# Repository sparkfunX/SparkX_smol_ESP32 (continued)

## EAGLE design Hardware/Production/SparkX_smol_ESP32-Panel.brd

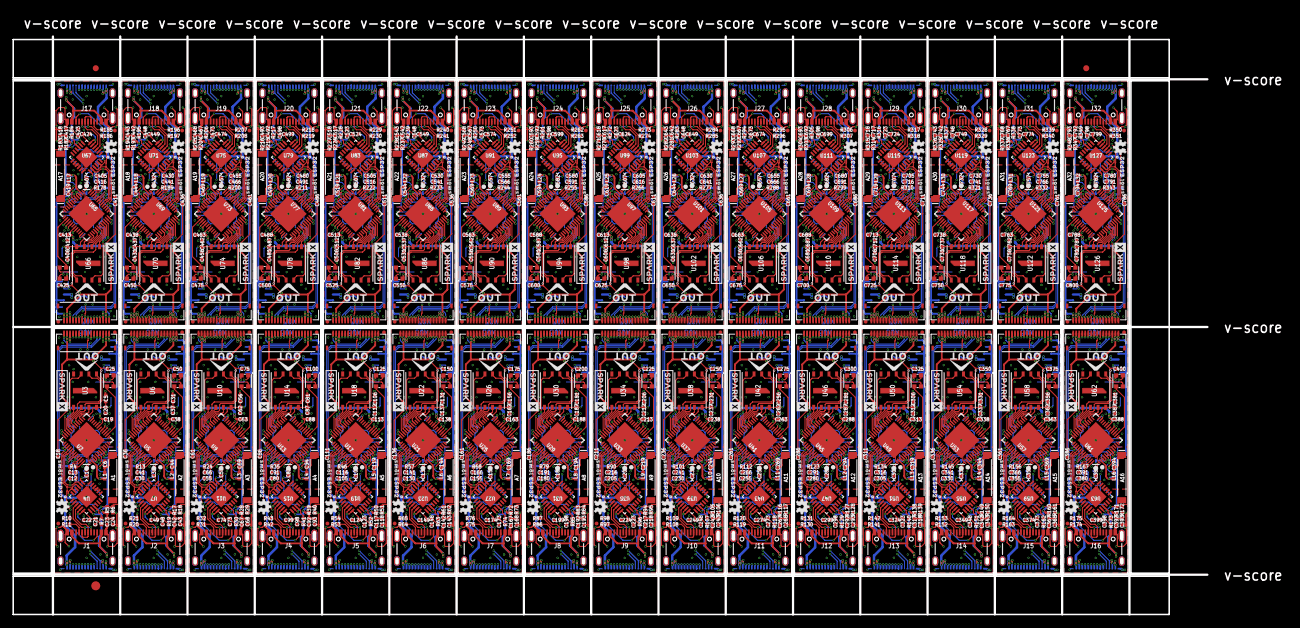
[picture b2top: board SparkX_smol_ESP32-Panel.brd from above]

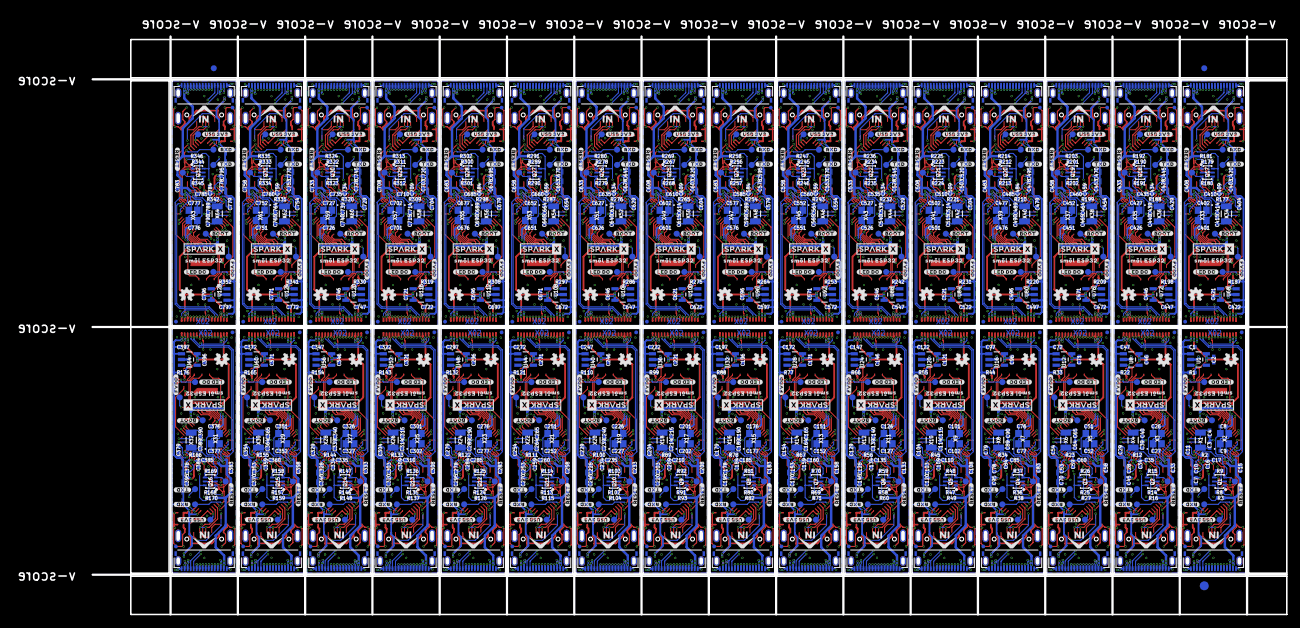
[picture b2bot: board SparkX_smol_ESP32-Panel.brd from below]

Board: 4 copper layers, 198.4 x 96.0 mm, 2470 parts (1379 on the bottom side), 1600 nets.

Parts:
!BOOT!, !BOOT!1, !BOOT!2, !BOOT!3, !BOOT!4, !BOOT!5, !BOOT!6, !BOOT!7, !BOOT!8, !BOOT!9, !BOOT!10, !BOOT!11, !BOOT!12, !BOOT!13, !BOOT!14, !BOOT!15, !BOOT!16, !BOOT!17, !BOOT!18, !BOOT!19, !BOOT!20, !BOOT!21, !BOOT!22, !BOOT!23, !BOOT!24, !BOOT!25, !BOOT!26, !BOOT!27, !BOOT!28, !BOOT!29, !BOOT!30, !BOOT!31: TEST-POINT3X4; PAD.03X.04
!RESET!, !RESET!1, !RESET!2, !RESET!3, !RESET!4, !RESET!5, !RESET!6, !RESET!7, !RESET!8, !RESET!9, !RESET!10, !RESET!11, !RESET!12, !RESET!13, !RESET!14, !RESET!15, !RESET!16, !RESET!17, !RESET!18, !RESET!19, !RESET!20, !RESET!21, !RESET!22, !RESET!23, !RESET!24, !RESET!25, !RESET!26, !RESET!27, !RESET!28, !RESET!29, !RESET!30, !RESET!31: TEST-POINT3X4; PAD.03X.04
A1, A2, A3, A4, A5, A6, A7, A8, A9, A10, A11, A12, A13, A14, A15, A16, A17, A18, A19, A20, A21, A22, A23, A24, A25, A26, A27, A28, A29, A30, A31, A32: ANTENNA2.4GHZ-8.0X1.0MM; ANT-2.4GHZ-8.0X1.0MM
C1, C2, C46, C47, C71, C72, C96, C97, C121, C122, C146, C147, C171, C172, C196, C197, C221, C222, C246, C247, C271, C272, C296, C297, C321, C322, C346, C347, C371, C372, C396, C397, C421, C422, C446, C447, C471, C472, C496, C497, C521, C522, C546, C547, C571, C572, C596, C597, C621, C622, C646, C647, C671, C672, C696, C697, C721, C722, C746, C747, C771, C772, C796, C797: 2.2uF; 0402-TIGHT
C3, C4, C39, C40, C64, C65, C89, C90, C114, C115, C139, C140, C164, C165, C189, C190, C214, C215, C239, C240, C264, C265, C289, C290, C314, C315, C339, C340, C364, C365, C389, C390, C414, C415, C439, C440, C464, C465, C489, C490, C514, C515, C539, C540, C564, C565, C589, C590, C614, C615, C639, C640, C664, C665, C689, C690, C714, C715, C739, C740, C764, C765, C789, C790: 15pF; 0402-TIGHT
C5, C15, C16, C18, C19, C22, C23, C25, C31, C33, C34, C36, C38, C42, C49, C50, C56, C58, C59, C61, C63, C67, C74, C75, C81, C83, C84, C86, C88, C92, C99, C100, C106, C108, C109, C111, C113, C117, C124, C125, C131, C133, C134, C136, C138, C142, C149, C150, C156, C158, C159, C161, C163, C167, C174, C175, C181, C183, C184, C186, C188, C192, C199, C200, C206, C208, C209, C211, C213, C217, C224, C225, C231, C233, C234, C236, C238, C242, C249, C250, C256, C258, C259, C261, C263, C267, C274, C275, C281, C283, C284, C286, C288, C292, C299, C300, C306, C308, C309, C311, C313, C317, C324, C325, C331, C333, C334, C336, C338, C342, C349, C350, C356, C358, C359, C361, C363, C367, C374, C375, C381, C383, C384, C386, C388, C392, C399, C400, C406, C408, C409, C411, C413, C417, C424, C425, C431, C433, C434, C436, C438, C442, C449, C450, C456, C458, C459, C461, C463, C467, C474, C475, C481, C483, C484, C486, C488, C492, C499, C500, C506, C508, C509, C511, C513, C517, C524, C525, C531, C533, C534, C536, C538, C542, C549, C550, C556, C558, C559, C561, C563, C567, C574, C575, C581, C583, C584, C586, C588, C592, C599, C600, C606, C608, C609, C611, C613, C617, C624, C625, C631, C633, C634, C636, C638, C642, C649, C650, C656, C658, C659, C661, C663, C667, C674, C675, C681, C683, C684, C686, C688, C692, C699, C700, C706, C708, C709, C711, C713, C717, C724, C725, C731, C733, C734, C736, C738, C742, C749, C750, C756, C758, C759, C761, C763, C767, C774, C775, C781, C783, C784, C786, C788, C792, C799, C800: 0.1uF; 0402-TIGHT
C6, C7, C44, C45, C69, C70, C94, C95, C119, C120, C144, C145, C169, C170, C194, C195, C219, C220, C244, C245, C269, C270, C294, C295, C319, C320, C344, C345, C369, C370, C394, C395, C419, C420, C444, C445, C469, C470, C494, C495, C519, C520, C544, C545, C569, C570, C594, C595, C619, C620, C644, C645, C669, C670, C694, C695, C719, C720, C744, C745, C769, C770, C794, C795: DNP; 0402-TIGHT_NO_CREAM
C8, C9, C26, C27, C51, C52, C76, C77, C101, C102, C126, C127, C151, C152, C176, C177, C201, C202, C226, C227, C251, C252, C276, C277, C301, C302, C326, C327, C351, C352, C376, C377, C401, C402, C426, C427, C451, C452, C476, C477, C501, C502, C526, C527, C551, C552, C576, C577, C601, C602, C626, C627, C651, C652, C676, C677, C701, C702, C726, C727, C751, C752, C776, C777: 12pF; 0402-TIGHT
C10, C11, C28, C29, C53, C54, C78, C79, C103, C104, C128, C129, C153, C154, C178, C179, C203, C204, C228, C229, C253, C254, C278, C279, C303, C304, C328, C329, C353, C354, C378, C379, C403, C404, C428, C429, C453, C454, C478, C479, C503, C504, C528, C529, C553, C554, C578, C579, C603, C604, C628, C629, C653, C654, C678, C679, C703, C704, C728, C729, C753, C754, C778, C779: 270pF; 0402-TIGHT
C12, C30, C55, C80, C105, C130, C155, C180, C205, C230, C255, C280, C305, C330, C355, C380, C405, C430, C455, C480, C505, C530, C555, C580, C605, C630, C655, C680, C705, C730, C755, C780: 10nF; 0402-TIGHT
C13, C41, C66, C91, C116, C141, C166, C191, C216, C241, C266, C291, C316, C341, C366, C391, C416, C441, C466, C491, C516, C541, C566, C591, C616, C641, C666, C691, C716, C741, C766, C791: 3.0nF; 0402-TIGHT
C14, C32, C57, C82, C107, C132, C157, C182, C207, C232, C257, C282, C307, C332, C357, C382, C407, C432, C457, C482, C507, C532, C557, C582, C607, C632, C657, C682, C707, C732, C757, C782: 100pF; 0402-TIGHT
C17, C35, C60, C85, C110, C135, C160, C185, C210, C235, C260, C285, C310, C335, C360, C385, C410, C435, C460, C485, C510, C535, C560, C585, C610, C635, C660, C685, C710, C735, C760, C785: 10uF; 0402-TIGHT
C20, C37, C62, C87, C112, C137, C162, C187, C212, C237, C262, C287, C312, C337, C362, C387, C412, C437, C462, C487, C512, C537, C562, C587, C612, C637, C662, C687, C712, C737, C762, C787: 1.0uF; 0402-TIGHT
C21, C24, C43, C48, C68, C73, C93, C98, C118, C123, C143, C148, C168, C173, C193, C198, C218, C223, C243, C248, C268, C273, C293, C298, C318, C323, C343, C348, C368, C373, C393, C398, C418, C423, C443, C448, C468, C473, C493, C498, C518, C523, C543, C548, C568, C573, C593, C598, C618, C623, C643, C648, C668, C673, C693, C698, C718, C723, C743, C748, C768, C773, C793, C798: 4.7uF; 0402-TIGHT
D1, D2, D3, D4, D5, D6, D7, D8, D9, D10, D11, D12, D13, D14, D15, D16, D17, D18, D19, D20, D21, D22, D23, D24, D25, D26, D27, D28, D29, D30, D31, D32: WS2812_2020; WS2812-2020
E$1, E$2, E$3, E$4: FIDUCIAL-1X2
E$5, E$6: FIDUCIAL-1.5X3
FD1, FD2, FD3, FD4, FD5, FD6, FD7, FD8, FD9, FD10, FD11, FD12, FD13, FD14, FD15, FD16, FD17, FD18, FD19, FD20, FD21, FD22, FD23, FD24, FD25, FD26, FD27, FD28, FD29, FD30, FD31, FD32, FD33, FD34, FD35, FD36, FD37, FD38, FD39, FD40, FD41, FD42, FD43, FD44, FD45, FD46, FD47, FD48, FD49, FD50, FD51, FD52, FD53, FD54, FD55, FD56, FD57, FD58, FD59, FD60, FD61, FD62, FD63, FD64, FD65, FD66, FD67, FD68, FD69, FD70, FD71, FD72, FD73, FD74, FD75, FD76, FD77, FD78, FD79, FD80, FD81, FD82, FD83, FD84, FD85, FD86, FD87, FD88, FD89, FD90, FD91, FD92, FD93, FD94, FD95, FD96, FD97, FD98, FD99, FD100, FD101, FD102, FD103, FD104, FD105, FD106, FD107, FD108, FD109, FD110, FD111, FD112, FD113, FD114, FD115, FD116, FD117, FD118, FD119, FD120, FD121, FD122, FD123, FD124, FD125, FD126, FD127, FD128: FIDUCIALUFIDUCIAL; FIDUCIAL-MICRO
FLASH_VDD, FLASH_VDD1, FLASH_VDD2, FLASH_VDD3, FLASH_VDD4, FLASH_VDD5, FLASH_VDD6, FLASH_VDD7, FLASH_VDD8, FLASH_VDD9, FLASH_VDD10, FLASH_VDD11, FLASH_VDD12, FLASH_VDD13, FLASH_VDD14, FLASH_VDD15, FLASH_VDD16, FLASH_VDD17, FLASH_VDD18, FLASH_VDD19, FLASH_VDD20, FLASH_VDD21, FLASH_VDD22, FLASH_VDD23, FLASH_VDD24, FLASH_VDD25, FLASH_VDD26, FLASH_VDD27, FLASH_VDD28, FLASH_VDD29, FLASH_VDD30, FLASH_VDD31: TEST-POINT3X4; PAD.03X.04
IN, IN1, IN2, IN3, IN4, IN5, IN6, IN7, IN8, IN9, IN10, IN11, IN12, IN13, IN14, IN15, IN16, IN17, IN18, IN19, IN20, IN21, IN22, IN23, IN24, IN25, IN26, IN27, IN28, IN29, IN30, IN31: FPC_16_0.5MM
J1, J2, J3, J4, J5, J6, J7, J8, J9, J10, J11, J12, J13, J14, J15, J16, J17, J18, J19, J20, J21, J22, J23, J24, J25, J26, J27, J28, J29, J30, J31, J32: USB-C-16P_4LAYER-PADS
L1, L2, L3, L4, L5, L6, L7, L8, L9, L10, L11, L12, L13, L14, L15, L16, L17, L18, L19, L20, L21, L22, L23, L24, L25, L26, L27, L28, L29, L30, L31, L32: 0; 0402-TIGHT
LED_DO, LED_DO1, LED_DO2, LED_DO3, LED_DO4, LED_DO5, LED_DO6, LED_DO7, LED_DO8, LED_DO9, LED_DO10, LED_DO11, LED_DO12, LED_DO13, LED_DO14, LED_DO15, LED_DO16, LED_DO17, LED_DO18, LED_DO19, LED_DO20, LED_DO21, LED_DO22, LED_DO23, LED_DO24, LED_DO25, LED_DO26, LED_DO27, LED_DO28, LED_DO29, LED_DO30, LED_DO31: TEST-POINT3X4; PAD.03X.04
LOGO1, LOGO2, LOGO3, LOGO4, LOGO5, LOGO6, LOGO7, LOGO8, LOGO9, LOGO10, LOGO11, LOGO12, LOGO13, LOGO14, LOGO15, LOGO16, LOGO17, LOGO18, LOGO19, LOGO20, LOGO21, LOGO22, LOGO23, LOGO24, LOGO25, LOGO26, LOGO27, LOGO28, LOGO29, LOGO30, LOGO31, LOGO32, LOGO33, LOGO34, LOGO35, LOGO36, LOGO37, LOGO38, LOGO39, LOGO40, LOGO41, LOGO42, LOGO43, LOGO44, LOGO45, LOGO46, LOGO47, LOGO48, LOGO49, LOGO50, LOGO51, LOGO52, LOGO53, LOGO54, LOGO55, LOGO56, LOGO57, LOGO58, LOGO59, LOGO60, LOGO61, LOGO62, LOGO63, LOGO64: OSHW-LOGOMINI; OSHW-LOGO-MINI
OUT, OUT1, OUT2, OUT3, OUT4, OUT5, OUT6, OUT7, OUT8, OUT9, OUT10, OUT11, OUT12, OUT13, OUT14, OUT15, OUT16, OUT17, OUT18, OUT19, OUT20, OUT21, OUT22, OUT23, OUT24, OUT25, OUT26, OUT27, OUT28, OUT29, OUT30, OUT31: FPC_16_0.5MM
Q1, Q2, Q3, Q4, Q5, Q6, Q7, Q8, Q9, Q10, Q11, Q12, Q13, Q14, Q15, Q16, Q17, Q18, Q19, Q20, Q21, Q22, Q23, Q24, Q25, Q26, Q27, Q28, Q29, Q30, Q31, Q32: MBT3904DW1T1; SC70-6
R1, R22, R33, R44, R55, R66, R77, R88, R99, R110, R121, R132, R143, R154, R165, R176, R187, R198, R209, R220, R231, R242, R253, R264, R275, R286, R297, R308, R319, R330, R341, R352: 100k; 0402-TIGHT
R2, R3, R8, R9, R12, R14, R15, R16, R23, R25, R26, R27, R34, R36, R37, R38, R45, R47, R48, R49, R56, R58, R59, R60, R67, R69, R70, R71, R78, R80, R81, R82, R89, R91, R92, R93, R100, R102, R103, R104, R111, R113, R114, R115, R122, R124, R125, R126, R133, R135, R136, R137, R144, R146, R147, R148, R155, R157, R158, R159, R166, R168, R169, R170, R177, R179, R180, R181, R188, R190, R191, R192, R199, R201, R202, R203, R210, R212, R213, R214, R221, R223, R224, R225, R232, R234, R235, R236, R243, R245, R246, R247, R254, R256, R257, R258, R265, R267, R268, R269, R276, R278, R279, R280, R287, R289, R290, R291, R298, R300, R301, R302, R309, R311, R312, R313, R320, R322, R323, R324, R331, R333, R334, R335, R342, R344, R345, R346: 10k; 0402-TIGHT
R4, R13, R24, R35, R46, R57, R68, R79, R90, R101, R112, R123, R134, R145, R156, R167, R178, R189, R200, R211, R222, R233, R244, R255, R266, R277, R288, R299, R310, R321, R332, R343: 20k; 0402-TIGHT
R5, R17, R28, R39, R50, R61, R72, R83, R94, R105, R116, R127, R138, R149, R160, R171, R182, R193, R204, R215, R226, R237, R248, R259, R270, R281, R292, R303, R314, R325, R336, R347: 22k; 0402-TIGHT
R6, R18, R29, R40, R51, R62, R73, R84, R95, R106, R117, R128, R139, R150, R161, R172, R183, R194, R205, R216, R227, R238, R249, R260, R271, R282, R293, R304, R315, R326, R337, R348: 33k; 0402-TIGHT
R7, R19, R30, R41, R52, R63, R74, R85, R96, R107, R118, R129, R140, R151, R162, R173, R184, R195, R206, R217, R228, R239, R250, R261, R272, R283, R294, R305, R316, R327, R338, R349: 2.2k; 0402-TIGHT
R10, R11, R20, R21, R31, R32, R42, R43, R53, R54, R64, R65, R75, R76, R86, R87, R97, R98, R108, R109, R119, R120, R130, R131, R141, R142, R152, R153, R163, R164, R174, R175, R185, R186, R196, R197, R207, R208, R218, R219, R229, R230, R240, R241, R251, R252, R262, R263, R273, R274, R284, R285, R295, R296, R306, R307, R317, R318, R328, R329, R339, R340, R350, R351: 5.1k; 0402-TIGHT
RXD, RXD1, RXD2, RXD3, RXD4, RXD5, RXD6, RXD7, RXD8, RXD9, RXD10, RXD11, RXD12, RXD13, RXD14, RXD15, RXD16, RXD17, RXD18, RXD19, RXD20, RXD21, RXD22, RXD23, RXD24, RXD25, RXD26, RXD27, RXD28, RXD29, RXD30, RXD31: TEST-POINT3X4; PAD.03X.04
TXD, TXD1, TXD2, TXD3, TXD4, TXD5, TXD6, TXD7, TXD8, TXD9, TXD10, TXD11, TXD12, TXD13, TXD14, TXD15, TXD16, TXD17, TXD18, TXD19, TXD20, TXD21, TXD22, TXD23, TXD24, TXD25, TXD26, TXD27, TXD28, TXD29, TXD30, TXD31: TEST-POINT3X4; PAD.03X.04
U1, U8, U12, U16, U20, U24, U28, U32, U36, U40, U44, U48, U52, U56, U60, U64, U68, U72, U76, U80, U84, U88, U92, U96, U100, U104, U108, U112, U116, U120, U124, U128: MIC5219 3.3V; SOT23-5
U2, U5, U9, U13, U17, U21, U25, U29, U33, U37, U41, U45, U49, U53, U57, U61, U65, U69, U73, U77, U81, U85, U89, U93, U97, U101, U105, U109, U113, U117, U121, U125: ESP32; QFN48-0.4MM
U3, U6, U10, U14, U18, U22, U26, U30, U34, U38, U42, U46, U50, U54, U58, U62, U66, U70, U74, U78, U82, U86, U90, U94, U98, U102, U106, U110, U114, U118, U122, U126: W25QXX128MBIT-6X5-SKINNY_CENTER; WSON-8-6X5-SKINNY_CENTERPAD
U4, U7, U11, U15, U19, U23, U27, U31, U35, U39, U43, U47, U51, U55, U59, U63, U67, U71, U75, U79, U83, U87, U91, U95, U99, U103, U107, U111, U115, U119, U123, U127: CP2102N; QFN24
U$1, U$2, U$3, U$4, U$31, U$32, U$46, U$47, U$61, U$62, U$76, U$77, U$91, U$92, U$106, U$107, U$121, U$122, U$136, U$137, U$151, U$152, U$166, U$167, U$181, U$182, U$196, U$197, U$211, U$212, U$226, U$227, U$241, U$242, U$256, U$257, U$271, U$272, U$286, U$287, U$301, U$302, U$316, U$317, U$331, U$332, U$346, U$347, U$361, U$362, U$376, U$377, U$391, U$392, U$406, U$407, U$421, U$422, U$436, U$437, U$451, U$452, U$466, U$467: SPARKX-LOGO3; SPARKX-SMALL
U$5, U$17, U$29, U$30, U$44, U$45, U$59, U$60, U$74, U$75, U$89, U$90, U$104, U$105, U$119, U$120, U$134, U$135, U$149, U$150, U$164, U$165, U$179, U$180, U$194, U$195, U$209, U$210, U$224, U$225, U$239, U$240, U$254, U$255, U$269, U$270, U$284, U$285, U$299, U$300, U$314, U$315, U$329, U$330, U$344, U$345, U$359, U$360, U$374, U$375, U$389, U$390, U$404, U$405, U$419, U$420, U$434, U$435, U$449, U$450, U$464, U$465, U$479, U$480: SM�L_ESP320
U$6, U$28, U$43, U$58, U$73, U$88, U$103, U$118, U$133, U$148, U$163, U$178, U$193, U$208, U$223, U$238, U$253, U$268, U$283, U$298, U$313, U$328, U$343, U$358, U$373, U$388, U$403, U$418, U$433, U$448, U$463, U$478: #TXD#0
U$7, U$18, U$33, U$48, U$63, U$78, U$93, U$108, U$123, U$138, U$153, U$168, U$183, U$198, U$213, U$228, U$243, U$258, U$273, U$288, U$303, U$318, U$333, U$348, U$363, U$378, U$393, U$408, U$423, U$438, U$453, U$468: ##BOOT##0
U$8, U$19, U$34, U$49, U$64, U$79, U$94, U$109, U$124, U$139, U$154, U$169, U$184, U$199, U$214, U$229, U$244, U$259, U$274, U$289, U$304, U$319, U$334, U$349, U$364, U$379, U$394, U$409, U$424, U$439, U$454, U$469: ##RESET##0
U$9, U$20, U$35, U$50, U$65, U$80, U$95, U$110, U$125, U$140, U$155, U$170, U$185, U$200, U$215, U$230, U$245, U$260, U$275, U$290, U$305, U$320, U$335, U$350, U$365, U$380, U$395, U$410, U$425, U$440, U$455, U$470: #USB_3V3#0
U$10, U$21, U$36, U$51, U$66, U$81, U$96, U$111, U$126, U$141, U$156, U$171, U$186, U$201, U$216, U$231, U$246, U$261, U$276, U$291, U$306, U$321, U$336, U$351, U$366, U$381, U$396, U$411, U$426, U$441, U$456, U$471: #FVDD#0
U$11, U$22, U$37, U$52, U$67, U$82, U$97, U$112, U$127, U$142, U$157, U$172, U$187, U$202, U$217, U$232, U$247, U$262, U$277, U$292, U$307, U$322, U$337, U$352, U$367, U$382, U$397, U$412, U$427, U$442, U$457, U$472: #LED_DO#0
U$12, U$26, U$41, U$56, U$71, U$86, U$101, U$116, U$131, U$146, U$161, U$176, U$191, U$206, U$221, U$236, U$251, U$266, U$281, U$296, U$311, U$326, U$341, U$356, U$371, U$386, U$401, U$416, U$431, U$446, U$461, U$476: IN0
U$13, U$25, U$40, U$55, U$70, U$85, U$100, U$115, U$130, U$145, U$160, U$175, U$190, U$205, U$220, U$235, U$250, U$265, U$280, U$295, U$310, U$325, U$340, U$355, U$370, U$385, U$400, U$415, U$430, U$445, U$460, U$475: OUT0
U$14, U$15, U$23, U$24, U$38, U$39, U$53, U$54, U$68, U$69, U$83, U$84, U$98, U$99, U$113, U$114, U$128, U$129, U$143, U$144, U$158, U$159, U$173, U$174, U$188, U$189, U$203, U$204, U$218, U$219, U$233, U$234, U$248, U$249, U$263, U$264, U$278, U$279, U$293, U$294, U$308, U$309, U$323, U$324, U$338, U$339, U$353, U$354, U$368, U$369, U$383, U$384, U$398, U$399, U$413, U$414, U$428, U$429, U$443, U$444, U$458, U$459, U$473, U$474: SMOL_LOGOSMALL; SMOL_SMALL
U$16, U$27, U$42, U$57, U$72, U$87, U$102, U$117, U$132, U$147, U$162, U$177, U$192, U$207, U$222, U$237, U$252, U$267, U$282, U$297, U$312, U$327, U$342, U$357, U$372, U$387, U$402, U$417, U$432, U$447, U$462, U$477: #RXD#0
USB_3V1, USB_3V2, USB_3V3, USB_3V4, USB_3V5, USB_3V6, USB_3V7, USB_3V8, USB_3V9, USB_3V10, USB_3V11, USB_3V12, USB_3V13, USB_3V14, USB_3V15, USB_3V16, USB_3V17, USB_3V18, USB_3V19, USB_3V20, USB_3V21, USB_3V22, USB_3V23, USB_3V24, USB_3V25, USB_3V26, USB_3V27, USB_3V28, USB_3V29, USB_3V30, USB_3V31, USB_3V32: TEST-POINT3X4; PAD.03X.04
X1, X4, X6, X8, X10, X12, X14, X16, X18, X20, X22, X24, X26, X28, X30, X32, X34, X36, X38, X40, X42, X44, X46, X48, X50, X52, X54, X56, X58, X60, X62, X64: 32.768kHz; CRYSTAL-SMD-3.2X1.5MM
X2, X3, X5, X7, X9, X11, X13, X15, X17, X19, X21, X23, X25, X27, X29, X31, X33, X35, X37, X39, X41, X43, X45, X47, X49, X51, X53, X55, X57, X59, X61, X63: 40MHz; CRYSTAL-SMD-2X2.5MM

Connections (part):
0-!BOOT!: !BOOT!.1, Q1.6, R3.1, U2.23
0-!BOOT!1: !BOOT!1.1, Q2.6, R16.1, U5.23
0-!BOOT!2: !BOOT!2.1, Q3.6, R27.1, U9.23
0-!BOOT!3: !BOOT!3.1, Q4.6, R38.1, U13.23
0-!BOOT!4: !BOOT!4.1, Q5.6, R49.1, U17.23
0-!BOOT!5: !BOOT!5.1, Q6.6, R60.1, U21.23
0-!BOOT!6: !BOOT!6.1, Q7.6, R71.1, U25.23
0-!BOOT!7: !BOOT!7.1, Q8.6, R82.1, U29.23
0-!BOOT!8: !BOOT!8.1, Q9.6, R93.1, U33.23
0-!BOOT!9: !BOOT!9.1, Q10.6, R104.1, U37.23
0-!BOOT!10: !BOOT!10.1, Q11.6, R115.1, U41.23
0-!BOOT!11: !BOOT!11.1, Q12.6, R126.1, U45.23
0-!BOOT!12: !BOOT!12.1, Q13.6, R137.1, U49.23
0-!BOOT!13: !BOOT!13.1, Q14.6, R148.1, U53.23
0-!BOOT!14: !BOOT!14.1, Q15.6, R159.1, U57.23
0-!BOOT!15: !BOOT!15.1, Q16.6, R170.1, U61.23
0-!BOOT!16: !BOOT!16.1, Q17.6, R181.1, U65.23
0-!BOOT!17: !BOOT!17.1, Q18.6, R192.1, U69.23
0-!BOOT!18: !BOOT!18.1, Q19.6, R203.1, U73.23
0-!BOOT!19: !BOOT!19.1, Q20.6, R214.1, U77.23
0-!BOOT!20: !BOOT!20.1, Q21.6, R225.1, U81.23
0-!BOOT!21: !BOOT!21.1, Q22.6, R236.1, U85.23
0-!BOOT!22: !BOOT!22.1, Q23.6, R247.1, U89.23
0-!BOOT!23: !BOOT!23.1, Q24.6, R258.1, U93.23
0-!BOOT!24: !BOOT!24.1, Q25.6, R269.1, U97.23
0-!BOOT!25: !BOOT!25.1, Q26.6, R280.1, U101.23
0-!BOOT!26: !BOOT!26.1, Q27.6, R291.1, U105.23
0-!BOOT!27: !BOOT!27.1, Q28.6, R302.1, U109.23
0-!BOOT!28: !BOOT!28.1, Q29.6, R313.1, U113.23
0-!BOOT!29: !BOOT!29.1, Q30.6, R324.1, U117.23
0-!BOOT!30: !BOOT!30.1, Q31.6, R335.1, U121.23
0-!BOOT!31: !BOOT!31.1, Q32.6, R346.1, U125.23
1: C11.1, U2.7
2: C29.1, U5.7
3: C10.2, U2.5
3.3V: C2.1, C14.1, C15.1, C16.1, C17.1, C18.1, C19.1, C25.1, D1.VCC, IN.2, IN.15, OUT.2, OUT.15, R2.2, R3.2, U1.5, U2.1, U2.3, U2.4, U2.19, U2.37, U2.43, U2.46
3.3V1: C32.1, C33.1, C34.1, C35.1, C36.1, C38.1, C46.1, C50.1, D2.VCC, IN1.2, IN1.15, OUT1.2, OUT1.15, R12.2, R16.2, U5.1, U5.3, U5.4, U5.19, U5.37, U5.43, U5.46, U8.5
3.3V2: C57.1, C58.1, C59.1, C60.1, C61.1, C63.1, C71.1, C75.1, D3.VCC, IN2.2, IN2.15, OUT2.2, OUT2.15, R23.2, R27.2, U9.1, U9.3, U9.4, U9.19, U9.37, U9.43, U9.46, U12.5
3.3V3: C82.1, C83.1, C84.1, C85.1, C86.1, C88.1, C96.1, C100.1, D4.VCC, IN3.2, IN3.15, OUT3.2, OUT3.15, R34.2, R38.2, U13.1, U13.3, U13.4, U13.19, U13.37, U13.43, U13.46, U16.5
3.3V4: C107.1, C108.1, C109.1, C110.1, C111.1, C113.1, C121.1, C125.1, D5.VCC, IN4.2, IN4.15, OUT4.2, OUT4.15, R45.2, R49.2, U17.1, U17.3, U17.4, U17.19, U17.37, U17.43, U17.46, U20.5
3.3V5: C132.1, C133.1, C134.1, C135.1, C136.1, C138.1, C146.1, C150.1, D6.VCC, IN5.2, IN5.15, OUT5.2, OUT5.15, R56.2, R60.2, U21.1, U21.3, U21.4, U21.19, U21.37, U21.43, U21.46, U24.5
3.3V6: C157.1, C158.1, C159.1, C160.1, C161.1, C163.1, C171.1, C175.1, D7.VCC, IN6.2, IN6.15, OUT6.2, OUT6.15, R67.2, R71.2, U25.1, U25.3, U25.4, U25.19, U25.37, U25.43, U25.46, U28.5
3.3V7: C182.1, C183.1, C184.1, C185.1, C186.1, C188.1, C196.1, C200.1, D8.VCC, IN7.2, IN7.15, OUT7.2, OUT7.15, R78.2, R82.2, U29.1, U29.3, U29.4, U29.19, U29.37, U29.43, U29.46, U32.5
3.3V8: C207.1, C208.1, C209.1, C210.1, C211.1, C213.1, C221.1, C225.1, D9.VCC, IN8.2, IN8.15, OUT8.2, OUT8.15, R89.2, R93.2, U33.1, U33.3, U33.4, U33.19, U33.37, U33.43, U33.46, U36.5
3.3V9: C232.1, C233.1, C234.1, C235.1, C236.1, C238.1, C246.1, C250.1, D10.VCC, IN9.2, IN9.15, OUT9.2, OUT9.15, R100.2, R104.2, U37.1, U37.3, U37.4, U37.19, U37.37, U37.43, U37.46, U40.5
3.3V10: C257.1, C258.1, C259.1, C260.1, C261.1, C263.1, C271.1, C275.1, D11.VCC, IN10.2, IN10.15, OUT10.2, OUT10.15, R111.2, R115.2, U41.1, U41.3, U41.4, U41.19, U41.37, U41.43, U41.46, U44.5
3.3V11: C282.1, C283.1, C284.1, C285.1, C286.1, C288.1, C296.1, C300.1, D12.VCC, IN11.2, IN11.15, OUT11.2, OUT11.15, R122.2, R126.2, U45.1, U45.3, U45.4, U45.19, U45.37, U45.43, U45.46, U48.5
3.3V12: C307.1, C308.1, C309.1, C310.1, C311.1, C313.1, C321.1, C325.1, D13.VCC, IN12.2, IN12.15, OUT12.2, OUT12.15, R133.2, R137.2, U49.1, U49.3, U49.4, U49.19, U49.37, U49.43, U49.46, U52.5
3.3V13: C332.1, C333.1, C334.1, C335.1, C336.1, C338.1, C346.1, C350.1, D14.VCC, IN13.2, IN13.15, OUT13.2, OUT13.15, R144.2, R148.2, U53.1, U53.3, U53.4, U53.19, U53.37, U53.43, U53.46, U56.5
3.3V14: C357.1, C358.1, C359.1, C360.1, C361.1, C363.1, C371.1, C375.1, D15.VCC, IN14.2, IN14.15, OUT14.2, OUT14.15, R155.2, R159.2, U57.1, U57.3, U57.4, U57.19, U57.37, U57.43, U57.46, U60.5
3.3V15: C382.1, C383.1, C384.1, C385.1, C386.1, C388.1, C396.1, C400.1, D16.VCC, IN15.2, IN15.15, OUT15.2, OUT15.15, R166.2, R170.2, U61.1, U61.3, U61.4, U61.19, U61.37, U61.43, U61.46, U64.5
3.3V16: C407.1, C408.1, C409.1, C410.1, C411.1, C413.1, C421.1, C425.1, D17.VCC, IN16.2, IN16.15, OUT16.2, OUT16.15, R177.2, R181.2, U65.1, U65.3, U65.4, U65.19, U65.37, U65.43, U65.46, U68.5
3.3V17: C432.1, C433.1, C434.1, C435.1, C436.1, C438.1, C446.1, C450.1, D18.VCC, IN17.2, IN17.15, OUT17.2, OUT17.15, R188.2, R192.2, U69.1, U69.3, U69.4, U69.19, U69.37, U69.43, U69.46, U72.5
3.3V18: C457.1, C458.1, C459.1, C460.1, C461.1, C463.1, C471.1, C475.1, D19.VCC, IN18.2, IN18.15, OUT18.2, OUT18.15, R199.2, R203.2, U73.1, U73.3, U73.4, U73.19, U73.37, U73.43, U73.46, U76.5
3.3V19: C482.1, C483.1, C484.1, C485.1, C486.1, C488.1, C496.1, C500.1, D20.VCC, IN19.2, IN19.15, OUT19.2, OUT19.15, R210.2, R214.2, U77.1, U77.3, U77.4, U77.19, U77.37, U77.43, U77.46, U80.5
3.3V20: C507.1, C508.1, C509.1, C510.1, C511.1, C513.1, C521.1, C525.1, D21.VCC, IN20.2, IN20.15, OUT20.2, OUT20.15, R221.2, R225.2, U81.1, U81.3, U81.4, U81.19, U81.37, U81.43, U81.46, U84.5
3.3V21: C532.1, C533.1, C534.1, C535.1, C536.1, C538.1, C546.1, C550.1, D22.VCC, IN21.2, IN21.15, OUT21.2, OUT21.15, R232.2, R236.2, U85.1, U85.3, U85.4, U85.19, U85.37, U85.43, U85.46, U88.5
3.3V22: C557.1, C558.1, C559.1, C560.1, C561.1, C563.1, C571.1, C575.1, D23.VCC, IN22.2, IN22.15, OUT22.2, OUT22.15, R243.2, R247.2, U89.1, U89.3, U89.4, U89.19, U89.37, U89.43, U89.46, U92.5
3.3V23: C582.1, C583.1, C584.1, C585.1, C586.1, C588.1, C596.1, C600.1, D24.VCC, IN23.2, IN23.15, OUT23.2, OUT23.15, R254.2, R258.2, U93.1, U93.3, U93.4, U93.19, U93.37, U93.43, U93.46, U96.5
3.3V24: C607.1, C608.1, C609.1, C610.1, C611.1, C613.1, C621.1, C625.1, D25.VCC, IN24.2, IN24.15, OUT24.2, OUT24.15, R265.2, R269.2, U97.1, U97.3, U97.4, U97.19, U97.37, U97.43, U97.46, U100.5
3.3V25: C632.1, C633.1, C634.1, C635.1, C636.1, C638.1, C646.1, C650.1, D26.VCC, IN25.2, IN25.15, OUT25.2, OUT25.15, R276.2, R280.2, U101.1, U101.3, U101.4, U101.19, U101.37, U101.43, U101.46, U104.5
3.3V26: C657.1, C658.1, C659.1, C660.1, C661.1, C663.1, C671.1, C675.1, D27.VCC, IN26.2, IN26.15, OUT26.2, OUT26.15, R287.2, R291.2, U105.1, U105.3, U105.4, U105.19, U105.37, U105.43, U105.46, U108.5
3.3V27: C682.1, C683.1, C684.1, C685.1, C686.1, C688.1, C696.1, C700.1, D28.VCC, IN27.2, IN27.15, OUT27.2, OUT27.15, R298.2, R302.2, U109.1, U109.3, U109.4, U109.19, U109.37, U109.43, U109.46, U112.5
3.3V28: C707.1, C708.1, C709.1, C710.1, C711.1, C713.1, C721.1, C725.1, D29.VCC, IN28.2, IN28.15, OUT28.2, OUT28.15, R309.2, R313.2, U113.1, U113.3, U113.4, U113.19, U113.37, U113.43, U113.46, U116.5
3.3V29: C732.1, C733.1, C734.1, C735.1, C736.1, C738.1, C746.1, C750.1, D30.VCC, IN29.2, IN29.15, OUT29.2, OUT29.15, R320.2, R324.2, U117.1, U117.3, U117.4, U117.19, U117.37, U117.43, U117.46, U120.5
3.3V30: C757.1, C758.1, C759.1, C760.1, C761.1, C763.1, C771.1, C775.1, D31.VCC, IN30.2, IN30.15, OUT30.2, OUT30.15, R331.2, R335.2, U121.1, U121.3, U121.4, U121.19, U121.37, U121.43, U121.46, U124.5
3.3V31: C782.1, C783.1, C784.1, C785.1, C786.1, C788.1, C796.1, C800.1, D32.VCC, IN31.2, IN31.15, OUT31.2, OUT31.15, R342.2, R346.2, U125.1, U125.3, U125.4, U125.19, U125.37, U125.43, U125.46, U128.5
4: C28.2, U5.5
5: C28.1, U5.6
6: C10.1, U2.6
7: C54.1, U9.7
8: C53.2, U9.5
9: C53.1, U9.6
10: C79.1, U13.7
11: C78.2, U13.5
12: C78.1, U13.6
13: C104.1, U17.7
14: C103.2, U17.5
15: C103.1, U17.6
16: C129.1, U21.7
17: C128.2, U21.5
18: C128.1, U21.6
19: C154.1, U25.7
20: C153.2, U25.5
21: C153.1, U25.6
22: C179.1, U29.7
23: C178.2, U29.5
24: C178.1, U29.6
25: C204.1, U33.7
26: C203.2, U33.5
27: C203.1, U33.6
28: C229.1, U37.7
29: C228.2, U37.5
30: C228.1, U37.6
31: C254.1, U41.7
32: C253.2, U41.5
32-RTC: C3.2, U2.12, X1.P$1
32-RTC1: C39.2, U5.12, X4.P$1
32-RTC2: C64.2, U9.12, X6.P$1
32-RTC3: C89.2, U13.12, X8.P$1
32-RTC4: C114.2, U17.12, X10.P$1
32-RTC5: C139.2, U21.12, X12.P$1
32-RTC6: C164.2, U25.12, X14.P$1
32-RTC7: C189.2, U29.12, X16.P$1
32-RTC8: C214.2, U33.12, X18.P$1
32-RTC9: C239.2, U37.12, X20.P$1
32-RTC10: C264.2, U41.12, X22.P$1
32-RTC11: C289.2, U45.12, X24.P$1
32-RTC12: C314.2, U49.12, X26.P$1
32-RTC13: C339.2, U53.12, X28.P$1
32-RTC14: C364.2, U57.12, X30.P$1
32-RTC15: C389.2, U61.12, X32.P$1
32-RTC16: C414.2, U65.12, X34.P$1
32-RTC17: C439.2, U69.12, X36.P$1
32-RTC18: C464.2, U73.12, X38.P$1
32-RTC19: C489.2, U77.12, X40.P$1
32-RTC20: C514.2, U81.12, X42.P$1
32-RTC21: C539.2, U85.12, X44.P$1
32-RTC22: C564.2, U89.12, X46.P$1
32-RTC23: C589.2, U93.12, X48.P$1
32-RTC24: C614.2, U97.12, X50.P$1
32-RTC25: C639.2, U101.12, X52.P$1
32-RTC26: C664.2, U105.12, X54.P$1
32-RTC27: C689.2, U109.12, X56.P$1
32-RTC28: C714.2, U113.12, X58.P$1
32-RTC29: C739.2, U117.12, X60.P$1
32-RTC30: C764.2, U121.12, X62.P$1
32-RTC31: C789.2, U125.12, X64.P$1
33: C253.1, U41.6
33-RTC: C4.2, U2.13, X1.P$2
33-RTC1: C40.2, U5.13, X4.P$2
33-RTC2: C65.2, U9.13, X6.P$2
33-RTC3: C90.2, U13.13, X8.P$2
33-RTC4: C115.2, U17.13, X10.P$2
33-RTC5: C140.2, U21.13, X12.P$2
33-RTC6: C165.2, U25.13, X14.P$2
33-RTC7: C190.2, U29.13, X16.P$2
33-RTC8: C215.2, U33.13, X18.P$2
33-RTC9: C240.2, U37.13, X20.P$2
33-RTC10: C265.2, U41.13, X22.P$2
33-RTC11: C290.2, U45.13, X24.P$2
33-RTC12: C315.2, U49.13, X26.P$2
33-RTC13: C340.2, U53.13, X28.P$2
33-RTC14: C365.2, U57.13, X30.P$2
33-RTC15: C390.2, U61.13, X32.P$2
33-RTC16: C415.2, U65.13, X34.P$2
33-RTC17: C440.2, U69.13, X36.P$2
33-RTC18: C465.2, U73.13, X38.P$2
33-RTC19: C490.2, U77.13, X40.P$2
33-RTC20: C515.2, U81.13, X42.P$2
33-RTC21: C540.2, U85.13, X44.P$2
33-RTC22: C565.2, U89.13, X46.P$2
33-RTC23: C590.2, U93.13, X48.P$2
33-RTC24: C615.2, U97.13, X50.P$2
33-RTC25: C640.2, U101.13, X52.P$2
33-RTC26: C665.2, U105.13, X54.P$2
33-RTC27: C690.2, U109.13, X56.P$2
33-RTC28: C715.2, U113.13, X58.P$2
33-RTC29: C740.2, U117.13, X60.P$2
33-RTC30: C765.2, U121.13, X62.P$2
33-RTC31: C790.2, U125.13, X64.P$2
34: C279.1, U45.7
35: C278.2, U45.5
36: C278.1, U45.6
37: C304.1, U49.7
38: C303.2, U49.5
39: C303.1, U49.6
40: C329.1, U53.7
41: C328.2, U53.5
42: C328.1, U53.6
43: C354.1, U57.7
44: C353.2, U57.5
45: C353.1, U57.6
46: C379.1, U61.7
47: C378.2, U61.5
48: C378.1, U61.6
49: C404.1, U65.7
50: C403.2, U65.5
51: C403.1, U65.6
52: C429.1, U69.7
53: C428.2, U69.5
54: C428.1, U69.6
55: C454.1, U73.7
56: C453.2, U73.5
57: C453.1, U73.6
58: C479.1, U77.7
59: C478.2, U77.5
60: C478.1, U77.6
61: C504.1, U81.7
62: C503.2, U81.5
63: C503.1, U81.6
64: C529.1, U85.7
65: C528.2, U85.5
66: C528.1, U85.6
67: C554.1, U89.7
68: C553.2, U89.5
69: C553.1, U89.6
70: C579.1, U93.7
71: C578.2, U93.5
72: C578.1, U93.6
73: C604.1, U97.7
74: C603.2, U97.5
75: C603.1, U97.6
76: C629.1, U101.7
77: C628.2, U101.5
78: C628.1, U101.6
79: C654.1, U105.7
80: C653.2, U105.5
81: C653.1, U105.6
82: C679.1, U109.7
83: C678.2, U109.5
84: C678.1, U109.6
85: C704.1, U113.7
86: C703.2, U113.5
87: C703.1, U113.6
88: C729.1, U117.7
89: C728.2, U117.5
90: C728.1, U117.6
91: C754.1, U121.7
92: C753.2, U121.5
93: C753.1, U121.6
94: C779.1, U125.7
95: C778.2, U125.5
96: C778.1, U125.6
!RESET: !RESET!.1, Q1.3, R2.1, U2.9
!RESET1: !RESET!1.1, Q2.3, R12.1, U5.9
!RESET2: !RESET!2.1, Q3.3, R23.1, U9.9
!RESET3: !RESET!3.1, Q4.3, R34.1, U13.9
!RESET4: !RESET!4.1, Q5.3, R45.1, U17.9
!RESET5: !RESET!5.1, Q6.3, R56.1, U21.9
!RESET6: !RESET!6.1, Q7.3, R67.1, U25.9
!RESET7: !RESET!7.1, Q8.3, R78.1, U29.9
!RESET8: !RESET!8.1, Q9.3, R89.1, U33.9
!RESET9: !RESET!9.1, Q10.3, R100.1, U37.9
!RESET10: !RESET!10.1, Q11.3, R111.1, U41.9
!RESET11: !RESET!11.1, Q12.3, R122.1, U45.9
!RESET12: !RESET!12.1, Q13.3, R133.1, U49.9
!RESET13: !RESET!13.1, Q14.3, R144.1, U53.9
!RESET14: !RESET!14.1, Q15.3, R155.1, U57.9
!RESET15: !RESET!15.1, Q16.3, R166.1, U61.9
!RESET16: !RESET!16.1, Q17.3, R177.1, U65.9
!RESET17: !RESET!17.1, Q18.3, R188.1, U69.9
!RESET18: !RESET!18.1, Q19.3, R199.1, U73.9
!RESET19: !RESET!19.1, Q20.3, R210.1, U77.9
!RESET20: !RESET!20.1, Q21.3, R221.1, U81.9
!RESET21: !RESET!21.1, Q22.3, R232.1, U85.9
!RESET22: !RESET!22.1, Q23.3, R243.1, U89.9
!RESET23: !RESET!23.1, Q24.3, R254.1, U93.9
!RESET24: !RESET!24.1, Q25.3, R265.1, U97.9
!RESET25: !RESET!25.1, Q26.3, R276.1, U101.9
!RESET26: !RESET!26.1, Q27.3, R287.1, U105.9
!RESET27: !RESET!27.1, Q28.3, R298.1, U109.9
!RESET28: !RESET!28.1, Q29.3, R309.1, U113.9
!RESET29: !RESET!29.1, Q30.3, R320.1, U117.9
!RESET30: !RESET!30.1, Q31.3, R331.1, U121.9
!RESET31: !RESET!31.1, Q32.3, R342.1, U125.9
CAP_10N1: C12.2, C13.1, R4.2, U2.48
CAP_10N2: C30.2, C41.1, R13.2, U5.48
CAP_10N3: C55.2, C66.1, R24.2, U9.48
CAP_10N4: C80.2, C91.1, R35.2, U13.48
CAP_10N5: C105.2, C116.1, R46.2, U17.48
CAP_10N6: C130.2, C141.1, R57.2, U21.48
CAP_10N7: C155.2, C166.1, R68.2, U25.48
CAP_10N8: C180.2, C191.1, R79.2, U29.48
CAP_10N9: C205.2, C216.1, R90.2, U33.48
CAP_10N10: C230.2, C241.1, R101.2, U37.48
CAP_10N11: C255.2, C266.1, R112.2, U41.48
CAP_10N12: C280.2, C291.1, R123.2, U45.48
CAP_10N13: C305.2, C316.1, R134.2, U49.48
CAP_10N14: C330.2, C341.1, R145.2, U53.48
CAP_10N15: C355.2, C366.1, R156.2, U57.48
CAP_10N16: C380.2, C391.1, R167.2, U61.48
CAP_10N17: C405.2, C416.1, R178.2, U65.48
CAP_10N18: C430.2, C441.1, R189.2, U69.48
CAP_10N19: C455.2, C466.1, R200.2, U73.48
CAP_10N20: C480.2, C491.1, R211.2, U77.48
CAP_10N21: C505.2, C516.1, R222.2, U81.48
CAP_10N22: C530.2, C541.1, R233.2, U85.48
CAP_10N23: C555.2, C566.1, R244.2, U89.48
CAP_10N24: C580.2, C591.1, R255.2, U93.48
CAP_10N25: C605.2, C616.1, R266.2, U97.48
CAP_10N26: C630.2, C641.1, R277.2, U101.48
CAP_10N27: C655.2, C666.1, R288.2, U105.48
CAP_10N28: C680.2, C691.1, R299.2, U109.48
CAP_10N29: C705.2, C716.1, R310.2, U113.48
CAP_10N30: C730.2, C741.1, R321.2, U117.48
CAP_10N31: C755.2, C766.1, R332.2, U121.48
CAP_10N32: C780.2, C791.1, R343.2, U125.48
CIPO: IN.6, OUT.6, U2.38
CIPO1: IN1.6, OUT1.6, U5.38
CIPO2: IN2.6, OUT2.6, U9.38
CIPO3: IN3.6, OUT3.6, U13.38
CIPO4: IN4.6, OUT4.6, U17.38
CIPO5: IN5.6, OUT5.6, U21.38
CIPO6: IN6.6, OUT6.6, U25.38
CIPO7: IN7.6, OUT7.6, U29.38
CIPO8: IN8.6, OUT8.6, U33.38
CIPO9: IN9.6, OUT9.6, U37.38
CIPO10: IN10.6, OUT10.6, U41.38
CIPO11: IN11.6, OUT11.6, U45.38
CIPO12: IN12.6, OUT12.6, U49.38
CIPO13: IN13.6, OUT13.6, U53.38
CIPO14: IN14.6, OUT14.6, U57.38
CIPO15: IN15.6, OUT15.6, U61.38
CIPO16: IN16.6, OUT16.6, U65.38
CIPO17: IN17.6, OUT17.6, U69.38
CIPO18: IN18.6, OUT18.6, U73.38
CIPO19: IN19.6, OUT19.6, U77.38
CIPO20: IN20.6, OUT20.6, U81.38
CIPO21: IN21.6, OUT21.6, U85.38
CIPO22: IN22.6, OUT22.6, U89.38
CIPO23: IN23.6, OUT23.6, U93.38
CIPO24: IN24.6, OUT24.6, U97.38
CIPO25: IN25.6, OUT25.6, U101.38
CIPO26: IN26.6, OUT26.6, U105.38
CIPO27: IN27.6, OUT27.6, U109.38
CIPO28: IN28.6, OUT28.6, U113.38
CIPO29: IN29.6, OUT29.6, U117.38
CIPO30: IN30.6, OUT30.6, U121.38
CIPO31: IN31.6, OUT31.6, U125.38
COPI: IN.5, OUT.5, U2.36
COPI1: IN1.5, OUT1.5, U5.36
COPI2: IN2.5, OUT2.5, U9.36
COPI3: IN3.5, OUT3.5, U13.36
COPI4: IN4.5, OUT4.5, U17.36
COPI5: IN5.5, OUT5.5, U21.36
COPI6: IN6.5, OUT6.5, U25.36
COPI7: IN7.5, OUT7.5, U29.36
COPI8: IN8.5, OUT8.5, U33.36
COPI9: IN9.5, OUT9.5, U37.36
COPI10: IN10.5, OUT10.5, U41.36
COPI11: IN11.5, OUT11.5, U45.36
COPI12: IN12.5, OUT12.5, U49.36
COPI13: IN13.5, OUT13.5, U53.36
COPI14: IN14.5, OUT14.5, U57.36
COPI15: IN15.5, OUT15.5, U61.36
COPI16: IN16.5, OUT16.5, U65.36
COPI17: IN17.5, OUT17.5, U69.36
COPI18: IN18.5, OUT18.5, U73.36
COPI19: IN19.5, OUT19.5, U77.36
COPI20: IN20.5, OUT20.5, U81.36
COPI21: IN21.5, OUT21.5, U85.36
COPI22: IN22.5, OUT22.5, U89.36
COPI23: IN23.5, OUT23.5, U93.36
COPI24: IN24.5, OUT24.5, U97.36
COPI25: IN25.5, OUT25.5, U101.36
COPI26: IN26.5, OUT26.5, U105.36
COPI27: IN27.5, OUT27.5, U109.36
COPI28: IN28.5, OUT28.5, U113.36
COPI29: IN29.5, OUT29.5, U117.36
COPI30: IN30.5, OUT30.5, U121.36
COPI31: IN31.5, OUT31.5, U125.36
CS0: IN.7, OUT.7, U2.34
CS1: IN.8, OUT.8, U2.17
CS2: IN.9, OUT.9, U2.20
CS3: IN1.7, OUT1.7, U5.34
CS4: IN1.8, OUT1.8, U5.17
CS5: IN1.9, OUT1.9, U5.20
CS6: IN2.7, OUT2.7, U9.34
CS7: IN2.8, OUT2.8, U9.17
CS8: IN2.9, OUT2.9, U9.20
CS9: IN3.7, OUT3.7, U13.34
CS10: IN3.8, OUT3.8, U13.17
CS11: IN3.9, OUT3.9, U13.20
CS12: IN4.7, OUT4.7, U17.34
CS13: IN4.8, OUT4.8, U17.17
CS14: IN4.9, OUT4.9, U17.20
CS15: IN5.7, OUT5.7, U21.34
CS16: IN5.8, OUT5.8, U21.17
CS17: IN5.9, OUT5.9, U21.20
CS18: IN6.7, OUT6.7, U25.34
CS19: IN6.8, OUT6.8, U25.17
CS20: IN6.9, OUT6.9, U25.20
CS21: IN7.7, OUT7.7, U29.34
CS22: IN7.8, OUT7.8, U29.17
CS23: IN7.9, OUT7.9, U29.20
CS24: IN8.7, OUT8.7, U33.34
CS25: IN8.8, OUT8.8, U33.17
CS26: IN8.9, OUT8.9, U33.20
CS27: IN9.7, OUT9.7, U37.34
CS28: IN9.8, OUT9.8, U37.17
CS29: IN9.9, OUT9.9, U37.20
CS30: IN10.7, OUT10.7, U41.34
CS31: IN10.8, OUT10.8, U41.17
CS32: IN10.9, OUT10.9, U41.20
CS33: IN11.7, OUT11.7, U45.34
CS34: IN11.8, OUT11.8, U45.17
CS35: IN11.9, OUT11.9, U45.20
CS36: IN12.7, OUT12.7, U49.34
CS37: IN12.8, OUT12.8, U49.17
CS38: IN12.9, OUT12.9, U49.20
CS39: IN13.7, OUT13.7, U53.34
CS40: IN13.8, OUT13.8, U53.17
CS41: IN13.9, OUT13.9, U53.20
CS42: IN14.7, OUT14.7, U57.34
CS43: IN14.8, OUT14.8, U57.17
CS44: IN14.9, OUT14.9, U57.20
CS45: IN15.7, OUT15.7, U61.34
CS46: IN15.8, OUT15.8, U61.17
CS47: IN15.9, OUT15.9, U61.20
CS48: IN16.7, OUT16.7, U65.34
CS49: IN16.8, OUT16.8, U65.17
CS50: IN16.9, OUT16.9, U65.20
CS51: IN17.7, OUT17.7, U69.34
CS52: IN17.8, OUT17.8, U69.17
CS53: IN17.9, OUT17.9, U69.20
CS54: IN18.7, OUT18.7, U73.34
CS55: IN18.8, OUT18.8, U73.17
CS56: IN18.9, OUT18.9, U73.20
CS57: IN19.7, OUT19.7, U77.34
CS58: IN19.8, OUT19.8, U77.17
CS59: IN19.9, OUT19.9, U77.20
CS60: IN20.7, OUT20.7, U81.34
CS61: IN20.8, OUT20.8, U81.17
CS62: IN20.9, OUT20.9, U81.20
CS63: IN21.7, OUT21.7, U85.34
CS64: IN21.8, OUT21.8, U85.17
CS65: IN21.9, OUT21.9, U85.20
CS66: IN22.7, OUT22.7, U89.34
CS67: IN22.8, OUT22.8, U89.17
CS68: IN22.9, OUT22.9, U89.20
CS69: IN23.7, OUT23.7, U93.34
CS70: IN23.8, OUT23.8, U93.17
CS71: IN23.9, OUT23.9, U93.20
CS72: IN24.7, OUT24.7, U97.34
CS73: IN24.8, OUT24.8, U97.17
CS74: IN24.9, OUT24.9, U97.20
CS75: IN25.7, OUT25.7, U101.34
CS76: IN25.8, OUT25.8, U101.17
CS77: IN25.9, OUT25.9, U101.20
CS78: IN26.7, OUT26.7, U105.34
CS79: IN26.8, OUT26.8, U105.17
CS80: IN26.9, OUT26.9, U105.20
CS81: IN27.7, OUT27.7, U109.34
CS82: IN27.8, OUT27.8, U109.17
CS83: IN27.9, OUT27.9, U109.20
CS84: IN28.7, OUT28.7, U113.34
CS85: IN28.8, OUT28.8, U113.17
CS86: IN28.9, OUT28.9, U113.20
CS87: IN29.7, OUT29.7, U117.34
CS88: IN29.8, OUT29.8, U117.17
CS89: IN29.9, OUT29.9, U117.20
CS90: IN30.7, OUT30.7, U121.34
CS91: IN30.8, OUT30.8, U121.17
CS92: IN30.9, OUT30.9, U121.20
CS93: IN31.7, OUT31.7, U125.34
CS94: IN31.8, OUT31.8, U125.17
CS95: IN31.9, OUT31.9, U125.20
D+: J1.A6, J1.B6, U4.3
D+1: J2.A6, J2.B6, U7.3
D+2: J3.A6, J3.B6, U11.3
D+3: J4.A6, J4.B6, U15.3
D+4: J5.A6, J5.B6, U19.3
D+5: J6.A6, J6.B6, U23.3
D+6: J7.A6, J7.B6, U27.3
D+7: J8.A6, J8.B6, U31.3
D+8: J9.A6, J9.B6, U35.3
D+9: J10.A6, J10.B6, U39.3
D+10: J11.A6, J11.B6, U43.3
D+11: J12.A6, J12.B6, U47.3
D+12: J13.A6, J13.B6, U51.3
D+13: J14.A6, J14.B6, U55.3
D+14: J15.A6, J15.B6, U59.3
D+15: J16.A6, J16.B6, U63.3
D+16: J17.A6, J17.B6, U67.3
D+17: J18.A6, J18.B6, U71.3
D+18: J19.A6, J19.B6, U75.3
D+19: J20.A6, J20.B6, U79.3
D+20: J21.A6, J21.B6, U83.3
D+21: J22.A6, J22.B6, U87.3
D+22: J23.A6, J23.B6, U91.3
D+23: J24.A6, J24.B6, U95.3
D+24: J25.A6, J25.B6, U99.3
D+25: J26.A6, J26.B6, U103.3
D+26: J27.A6, J27.B6, U107.3
D+27: J28.A6, J28.B6, U111.3
D+28: J29.A6, J29.B6, U115.3
D+29: J30.A6, J30.B6, U119.3
D+30: J31.A6, J31.B6, U123.3
D+31: J32.A6, J32.B6, U127.3
D-: J1.A7, J1.B7, U4.4
D-1: J2.A7, J2.B7, U7.4
D-2: J3.A7, J3.B7, U11.4
D-3: J4.A7, J4.B7, U15.4
D-4: J5.A7, J5.B7, U19.4
D-5: J6.A7, J6.B7, U23.4
D-6: J7.A7, J7.B7, U27.4
D-7: J8.A7, J8.B7, U31.4
D-8: J9.A7, J9.B7, U35.4
D-9: J10.A7, J10.B7, U39.4
D-10: J11.A7, J11.B7, U43.4
D-11: J12.A7, J12.B7, U47.4
D-12: J13.A7, J13.B7, U51.4
D-13: J14.A7, J14.B7, U55.4
D-14: J15.A7, J15.B7, U59.4
D-15: J16.A7, J16.B7, U63.4
D-16: J17.A7, J17.B7, U67.4
D-17: J18.A7, J18.B7, U71.4
D-18: J19.A7, J19.B7, U75.4
D-19: J20.A7, J20.B7, U79.4
D-20: J21.A7, J21.B7, U83.4
D-21: J22.A7, J22.B7, U87.4
D-22: J23.A7, J23.B7, U91.4
D-23: J24.A7, J24.B7, U95.4
D-24: J25.A7, J25.B7, U99.4
D-25: J26.A7, J26.B7, U103.4
D-26: J27.A7, J27.B7, U107.4
D-27: J28.A7, J28.B7, U111.4
D-28: J29.A7, J29.B7, U115.4
D-29: J30.A7, J30.B7, U119.4
D-30: J31.A7, J31.B7, U123.4
D-31: J32.A7, J32.B7, U127.4
DTR: Q1.1, R8.1, U4.23
DTR1: Q2.1, R14.1, U7.23
DTR2: Q3.1, R25.1, U11.23
DTR3: Q4.1, R36.1, U15.23
DTR4: Q5.1, R47.1, U19.23
DTR5: Q6.1, R58.1, U23.23
DTR6: Q7.1, R69.1, U27.23
DTR7: Q8.1, R80.1, U31.23
DTR8: Q9.1, R91.1, U35.23
DTR9: Q10.1, R102.1, U39.23
DTR10: Q11.1, R113.1, U43.23
DTR11: Q12.1, R124.1, U47.23
DTR12: Q13.1, R135.1, U51.23
DTR13: Q14.1, R146.1, U55.23
DTR14: Q15.1, R157.1, U59.23
DTR15: Q16.1, R168.1, U63.23
DTR16: Q17.1, R179.1, U67.23
DTR17: Q18.1, R190.1, U71.23
DTR18: Q19.1, R201.1, U75.23
DTR19: Q20.1, R212.1, U79.23
DTR20: Q21.1, R223.1, U83.23
DTR21: Q22.1, R234.1, U87.23
DTR22: Q23.1, R245.1, U91.23
DTR23: Q24.1, R256.1, U95.23
DTR24: Q25.1, R267.1, U99.23
DTR25: Q26.1, R278.1, U103.23
DTR26: Q27.1, R289.1, U107.23
DTR27: Q28.1, R300.1, U111.23
DTR28: Q29.1, R311.1, U115.23
DTR29: Q30.1, R322.1, U119.23
DTR30: Q31.1, R333.1, U123.23
DTR31: Q32.1, R344.1, U127.23
FLASH_SCK: U2.31, U3.6
FLASH_SCK1: U5.31, U6.6
FLASH_SCK2: U9.31, U10.6
FLASH_SCK3: U13.31, U14.6
FLASH_SCK4: U17.31, U18.6
FLASH_SCK5: U21.31, U22.6
FLASH_SCK6: U25.31, U26.6
FLASH_SCK7: U29.31, U30.6
FLASH_SCK8: U33.31, U34.6
FLASH_SCK9: U37.31, U38.6
FLASH_SCK10: U41.31, U42.6
FLASH_SCK11: U45.31, U46.6
FLASH_SCK12: U49.31, U50.6
FLASH_SCK13: U53.31, U54.6
FLASH_SCK14: U57.31, U58.6
FLASH_SCK15: U61.31, U62.6
FLASH_SCK16: U65.31, U66.6
FLASH_SCK17: U69.31, U70.6
FLASH_SCK18: U73.31, U74.6
FLASH_SCK19: U77.31, U78.6
FLASH_SCK20: U81.31, U82.6
FLASH_SCK21: U85.31, U86.6
FLASH_SCK22: U89.31, U90.6
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
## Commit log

2021-05-11 Work in progress
2021-05-11 Add CP2102 package outline
2021-05-12 Routed
2021-05-12 Ready for review
2021-05-13 Add neopixel. Add mirror-symmetric production panel
2021-05-14 Post-review updates
2021-05-27 Gapless production panel
2021-06-09 Updates for JLCPCB manufacture
2021-06-09 Update 16-way FPC Connector
2021-07-20 Add the first two examples
2021-07-21 Rename repo. Update README.
2021-08-20 X02 - add smôl branding
2021-09-29 Add Production_Test
2021-10-10 Auto-detect COM port. Use LED to show when SPIFFS and WiFi tests are complete
2021-10-11 Remove SPIFFS test from Production Test
2021-10-28 Add SKU and product image
2021-11-06 Add RGB_LED_Binary
